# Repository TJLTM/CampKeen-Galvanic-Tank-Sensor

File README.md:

# CampKeen-Galvanic-Tank-Sensor
Galvanic tank sensor pack for CampKeen

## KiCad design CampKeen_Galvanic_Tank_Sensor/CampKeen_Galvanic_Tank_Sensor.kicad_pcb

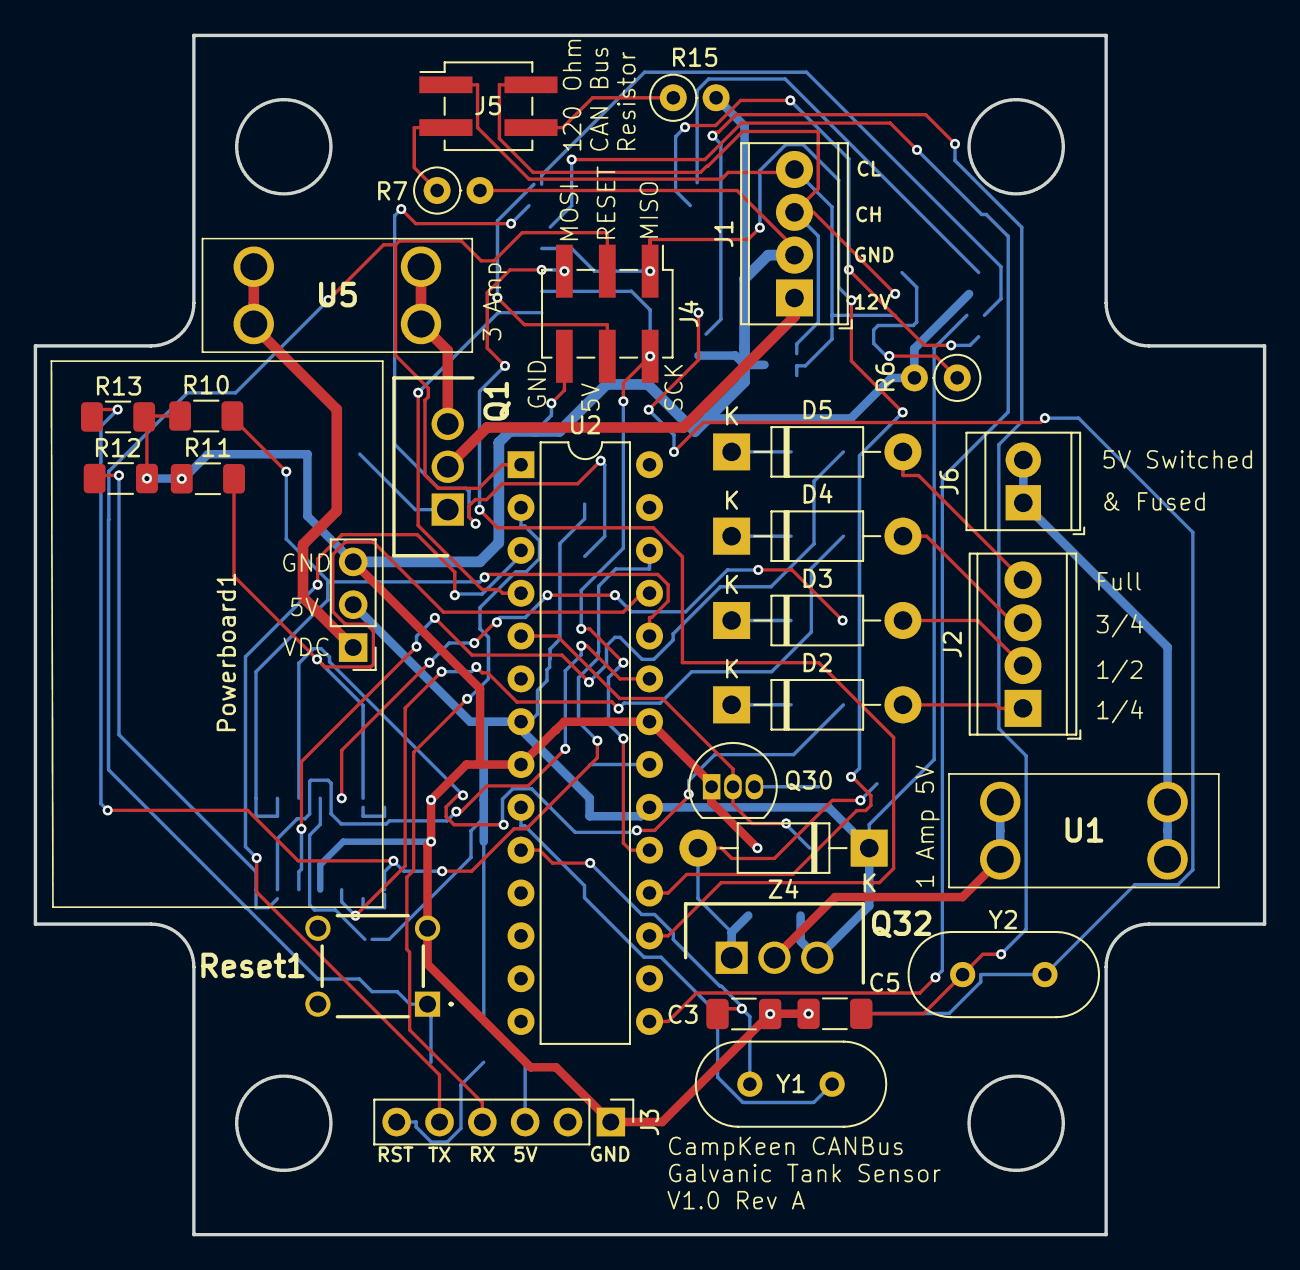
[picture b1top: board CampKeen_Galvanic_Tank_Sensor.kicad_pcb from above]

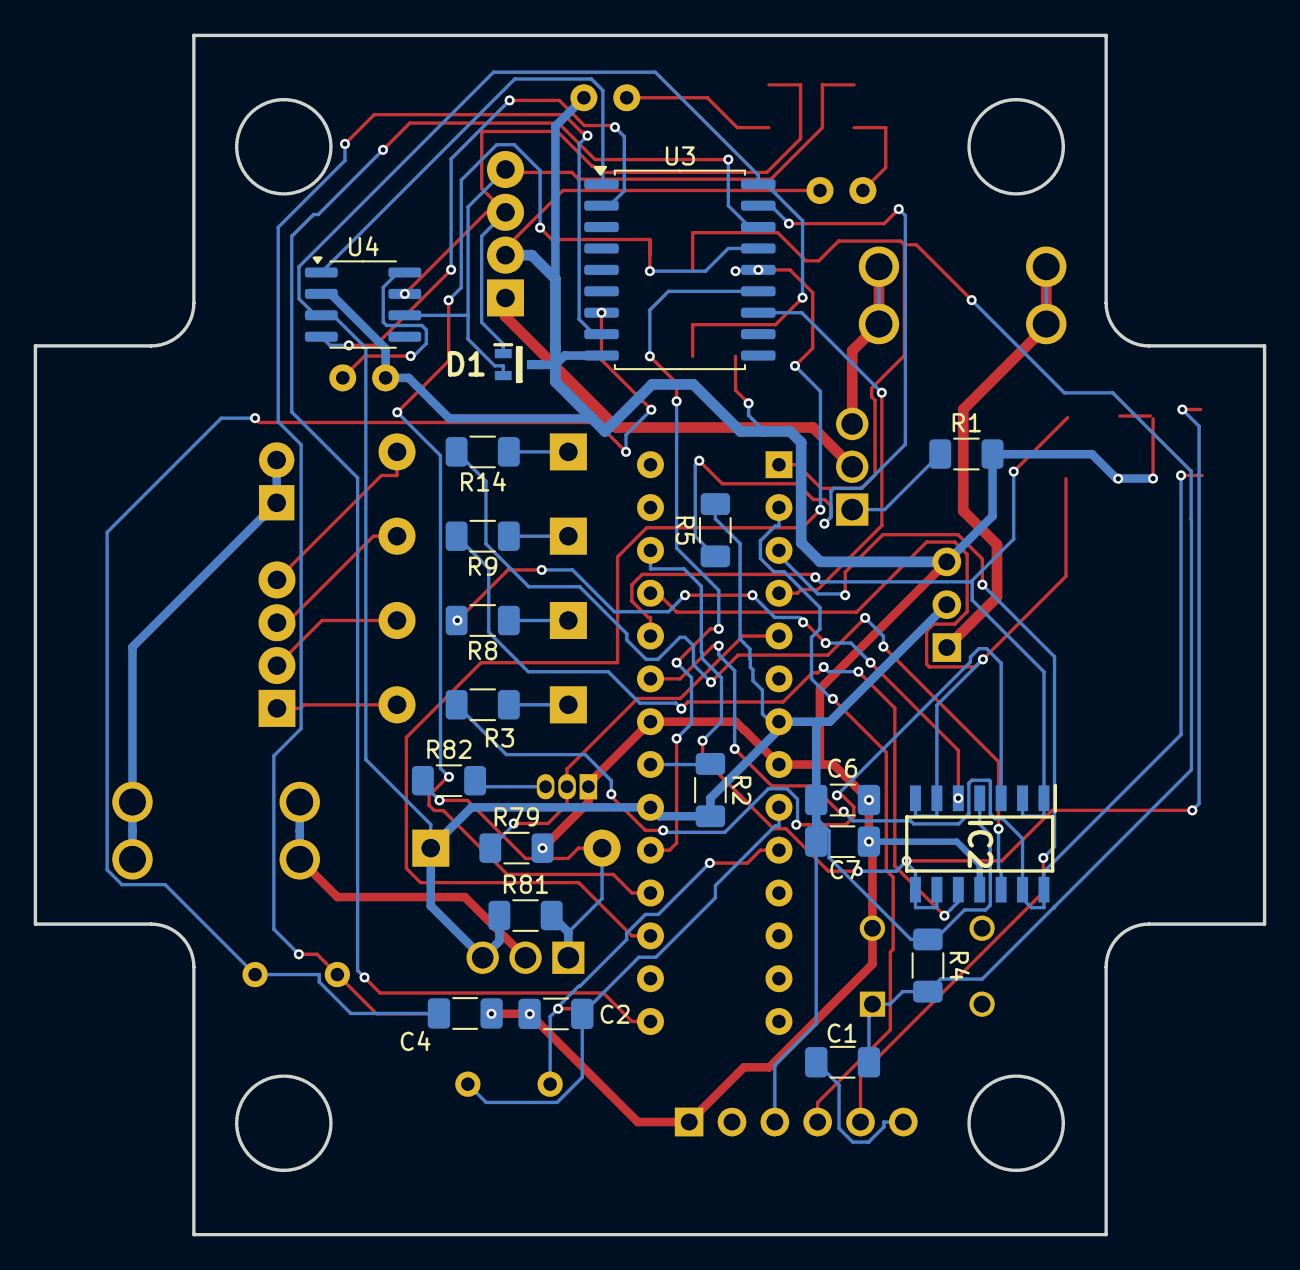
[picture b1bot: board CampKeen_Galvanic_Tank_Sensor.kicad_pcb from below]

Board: 2 copper layers, 72.9 x 71.1 mm, 50 parts (20 on the bottom side), 49 nets.

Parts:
C1, C6, C7: 100nf; C_1206_3216Metric_Pad1.33x1.80mm_HandSolder
C2, C3, C4, C5: 22pf; C_1206_3216Metric_Pad1.33x1.80mm_HandSolder
D1: PESD5V0L2UU,115; SOT65P210X110-3N
D2, D3, D4, D5: 1N4007; D_DO-41_SOD81_P10.16mm_Horizontal
IC2: OPA4340UA; SOIC127P600X175-14N
J1: Power_And_CAN; TerminalBlock_Phoenix_MPT-0,5-4-2.54_1x04_P2.54mm_Horizontal
J2: TankInputs; TerminalBlock_Phoenix_MPT-0,5-4-2.54_1x04_P2.54mm_Horizontal
J3: TTL_Programmer; PinHeader_1x06_P2.54mm_Vertical
J4: ICSP; PinHeader_2x03_P2.54mm_Vertical_SMD
J5: Conn_02x02_Counter_Clockwise; PinHeader_2x02_P2.54mm_Vertical_SMD
J6: Screw_Terminal_01x02; TerminalBlock_TE_282834-2_1x02_P2.54mm_Horizontal
Powerboard1: Conn_01x03; PinHeader_1x03_P2.54mm_Vertical
Q1, Q32: IRF9Z34NPBF; TO254P469X1042X1967-3P
Q30: 2N7000; TO-92_Inline
R1, R3, R4, R5, R8, R9, R14, R82: 10k; R_1206_3216Metric_Pad1.30x1.75mm_HandSolder
R2: 4.7k; R_1206_3216Metric_Pad1.30x1.75mm_HandSolder
R6: 17k; R_Axial_DIN0207_L6.3mm_D2.5mm_P2.54mm_Vertical
R7, R15: 60; R_Axial_DIN0207_L6.3mm_D2.5mm_P2.54mm_Vertical
R10, R11, R12, R13: 47K; R_1206_3216Metric_Pad1.30x1.75mm_HandSolder
R79: 1M; R_1206_3216Metric_Pad1.30x1.75mm_HandSolder
R81: 100k; R_1206_3216Metric_Pad1.30x1.75mm_HandSolder
Reset1: TS02-66-160-BK-260-LCR-D; TS0266160BK260LCRD
U1, U5: 3568
U2: ATmega328P-P; DIP-28_W7.62mm
U3: MCP2515-xSO; SOIC-18W_7.5x11.6mm_P1.27mm
U4: MCP2551-I-SN; SOIC-8_3.9x4.9mm_P1.27mm
Y1, Y2: 16MHz; Crystal_HC49-U_Vertical
Z4: BZX79C10; D_DO-41_SOD81_P10.16mm_Horizontal

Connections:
+5V: C6.1, C7.1, IC2.4 (V+), J3.3, J4.4, Powerboard1.2, Q32.3, R2.2, R4.1, R5.2, R81.1, U2.7 (VCC), U2.20 (AVCC), U3.18 (VDD), U4.3 (VDD), Z4.1
+VDC: Powerboard1.1, U5.3, U5.4
/BareMinAtmel328P/AREF: R2.1, U2.21 (AREF)
/BareMinAtmel328P/PB1-D9: U2.15 (PB1), U3.16 (~CS)
/BareMinAtmel328P/PB3-D11-MOSI: J4.5, U2.17 (PB3), U3.14 (SI)
/BareMinAtmel328P/PB4-D12-MISO: J4.1, U2.18 (PB4), U3.15 (SO)
/BareMinAtmel328P/PB5-D13-SCK: J4.2, U2.19 (PB5), U3.13 (SCK)
/BareMinAtmel328P/PC0-A0: IC2.13 (-IN_D), IC2.14 (OUT_D), R12.2, U2.23 (PC0)
/BareMinAtmel328P/PC1-A1: IC2.1 (OUT_A), IC2.2 (-IN_A), R10.2, U2.24 (PC1)
/BareMinAtmel328P/PC2-A2: IC2.6 (-IN_B), IC2.7 (OUT_B), R11.2, U2.25 (PC2)
/BareMinAtmel328P/PC3-A3: IC2.8 (OUT_C), IC2.9 (-IN_C), R13.2, U2.26 (PC3)
/BareMinAtmel328P/PD0-RX: J3.4, U2.2 (PD0)
/BareMinAtmel328P/PD1-TX: J3.5, U2.3 (PD1)
/BareMinAtmel328P/PD2-D2: U2.4 (PD2), U3.12 (~INT)
/BareMinAtmel328P/PD3-D3: Q30.2 (G), R79.1, U2.5 (PD3)
/BareMinAtmel328P/RESET: C1.2, J4.3, R4.2, Reset1.1 (NO_1), U2.1 (~RESET/PC6)
/BufferedADC/ADCIN1: IC2.3 (+IN_A), R3.2
/BufferedADC/ADCIN2: IC2.5 (+IN_B), R8.2
/BufferedADC/ADCIN3: IC2.10 (+IN_C), R9.2
/BufferedADC/ADCIN4: IC2.12 (+IN_D), R14.2
/CANBUS-MCP2515/RXtoCANTC: U3.2 (RXCAN), U4.4 (RXD)
/CANBUS-MCP2515/TXtoCANTC: U3.1 (TXCAN), U4.1 (TXD)
CANBUS_H: D1.1 (CATHODE_1), J1.3, J5.2, U4.7 (CANH)
CANBUS_L: D1.2 (CATHODE_2), J1.4, J5.1, U4.6 (CANL)
GND: C2.2, C3.2, C4.2, C5.2, C6.2, C7.2, D1.3 (COMMON_ANODE), IC2.11 (V-), J1.2, J3.1, J4.6, Powerboard1.3, Q30.1 (S), R1.2, R6.2, R7.2, R10.1, R11.1, R12.1, R13.1, R15.2, R79.2, Reset1.3 (COM_1), U2.8 (GND), U2.22 (GND), U3.9 (VSS), U4.2 (VSS)
unnamed: D2.2 (A), J2.1
unnamed: D2.1 (K), R3.1
unnamed: D3.2 (A), J2.2
unnamed: D3.1 (K), R8.1
unnamed: D4.2 (A), J2.3
unnamed: D4.1 (K), R9.1
unnamed: D5.2 (A), J2.4
unnamed: D5.1 (K), R14.1
unnamed: J1.1, Q1.2
unnamed: C1.1, J3.6
unnamed: J5.3, R7.1
unnamed: J5.4, R15.1
unnamed: J6.1, J6.2, U1.1, U1.2
unnamed: Q1.1, R1.1
unnamed: Q1.3, U5.1, U5.2
unnamed: Q30.3 (D), R82.2
unnamed: Q32.1, R81.2, R82.1, Z4.2
unnamed: Q32.2, U1.3, U1.4
unnamed: C2.1, U2.9 (XTAL1/PB6), Y1.2
unnamed: C3.1, U2.10 (XTAL2/PB7), Y1.1
unnamed: C5.1, U3.8 (OSC1), Y2.1
unnamed: C4.1, U3.7 (OSC2), Y2.2
unnamed: R5.1, U3.17 (~RESET)
unnamed: R6.1, U4.8 (Rs)
